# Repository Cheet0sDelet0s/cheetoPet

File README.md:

<h2 align="center"><u>cheetoPet</u></h2>

<h4 align="center"> an esp32 s3 based virtual pet </h4>

<p align="center">

<br>

</p>

### [+] notice
cheetoPet is being completely rebuilt. the pcb and software is still not finished. please star this project and come back to it later!

### [+] description
cheetoPet is a fully open-source modern tamagotchi. it features a 240*280 colour display, 3 face buttons + side rocker, 6 axis gyro and a speaker, all built on a custom pcb.

### [+] software
the software uses an abstraction layer that allows it to be ran on both esp32 and PC, where drivers for different devices can be easily created and swapped in. for PC, a lot of hardware that is present on the cheetoPet board is simulated, such as the gyro and battery. this is so the program runs as close to how it would natively. this is mostly to make development far easier, as constantly having to build the program and wait for it to upload to your esp32 takes a significant amount of time. being able to build and run it locally, while having access to regular c++ debugging tools, makes everything much less annoying.

### [+] building for pc
use the build.sh bash script in cheetoPet-V2:
`./build.sh`
you will need gcc and SDL2 installed. if the build is successful, the executable will run automatically. i develop on linux, so you may have issues if you are on windows/macos. if you are - why? without sounding like an annoying arch user (which i am), linux is simply better.

### [+] uploading to esp32
arduino IDE/CLI or the arduino vscode extension (what i use) is required to build and upload to the board. install the esp32 core in board manager, select esp32s3 dev module as your device, enable USB CDC on boot in tools and upload.

### [+] ordering pcb
i use JLCPCB for all my pcbs. they are simply the cheapest option available, but you can use any service really. just upload the gerbers and probably order a stencil to go with it. no specific board settings are needed really, though you may want to get a lower board thickness.

### [+] ordering parts
LCSC (sister company of jlcpcb)  is where i get my parts for this boardd. aliexpress unfortunately doesnt really work here. its a sad day for us all. there is a BOM you can upload however there are most likely a few parts on it that are out of stock. finding alternatives is fairly easy.

you must buy the battery and display separately. a 1S 1000mah lipo/ion is what the board expects. the display is a very specific ST7789 from BuyDisplay, you can find it on aliexpress thank GOD. https://www.aliexpress.com/item/1005008850313883.html
they are about $5-6 each.

### [+] ordering pcba
i probably wouldnt even bother assembling by hand like i did, however getting it assembled for you is just so expensive for low quantity orders. jlcpcb quoted me £150 ($200, not including battery and display cost) for 2 boards, when building 4 by hand costs £100. so unless you are ordering 1000 units, you are kind of screwed either way 🥰🥰🥰

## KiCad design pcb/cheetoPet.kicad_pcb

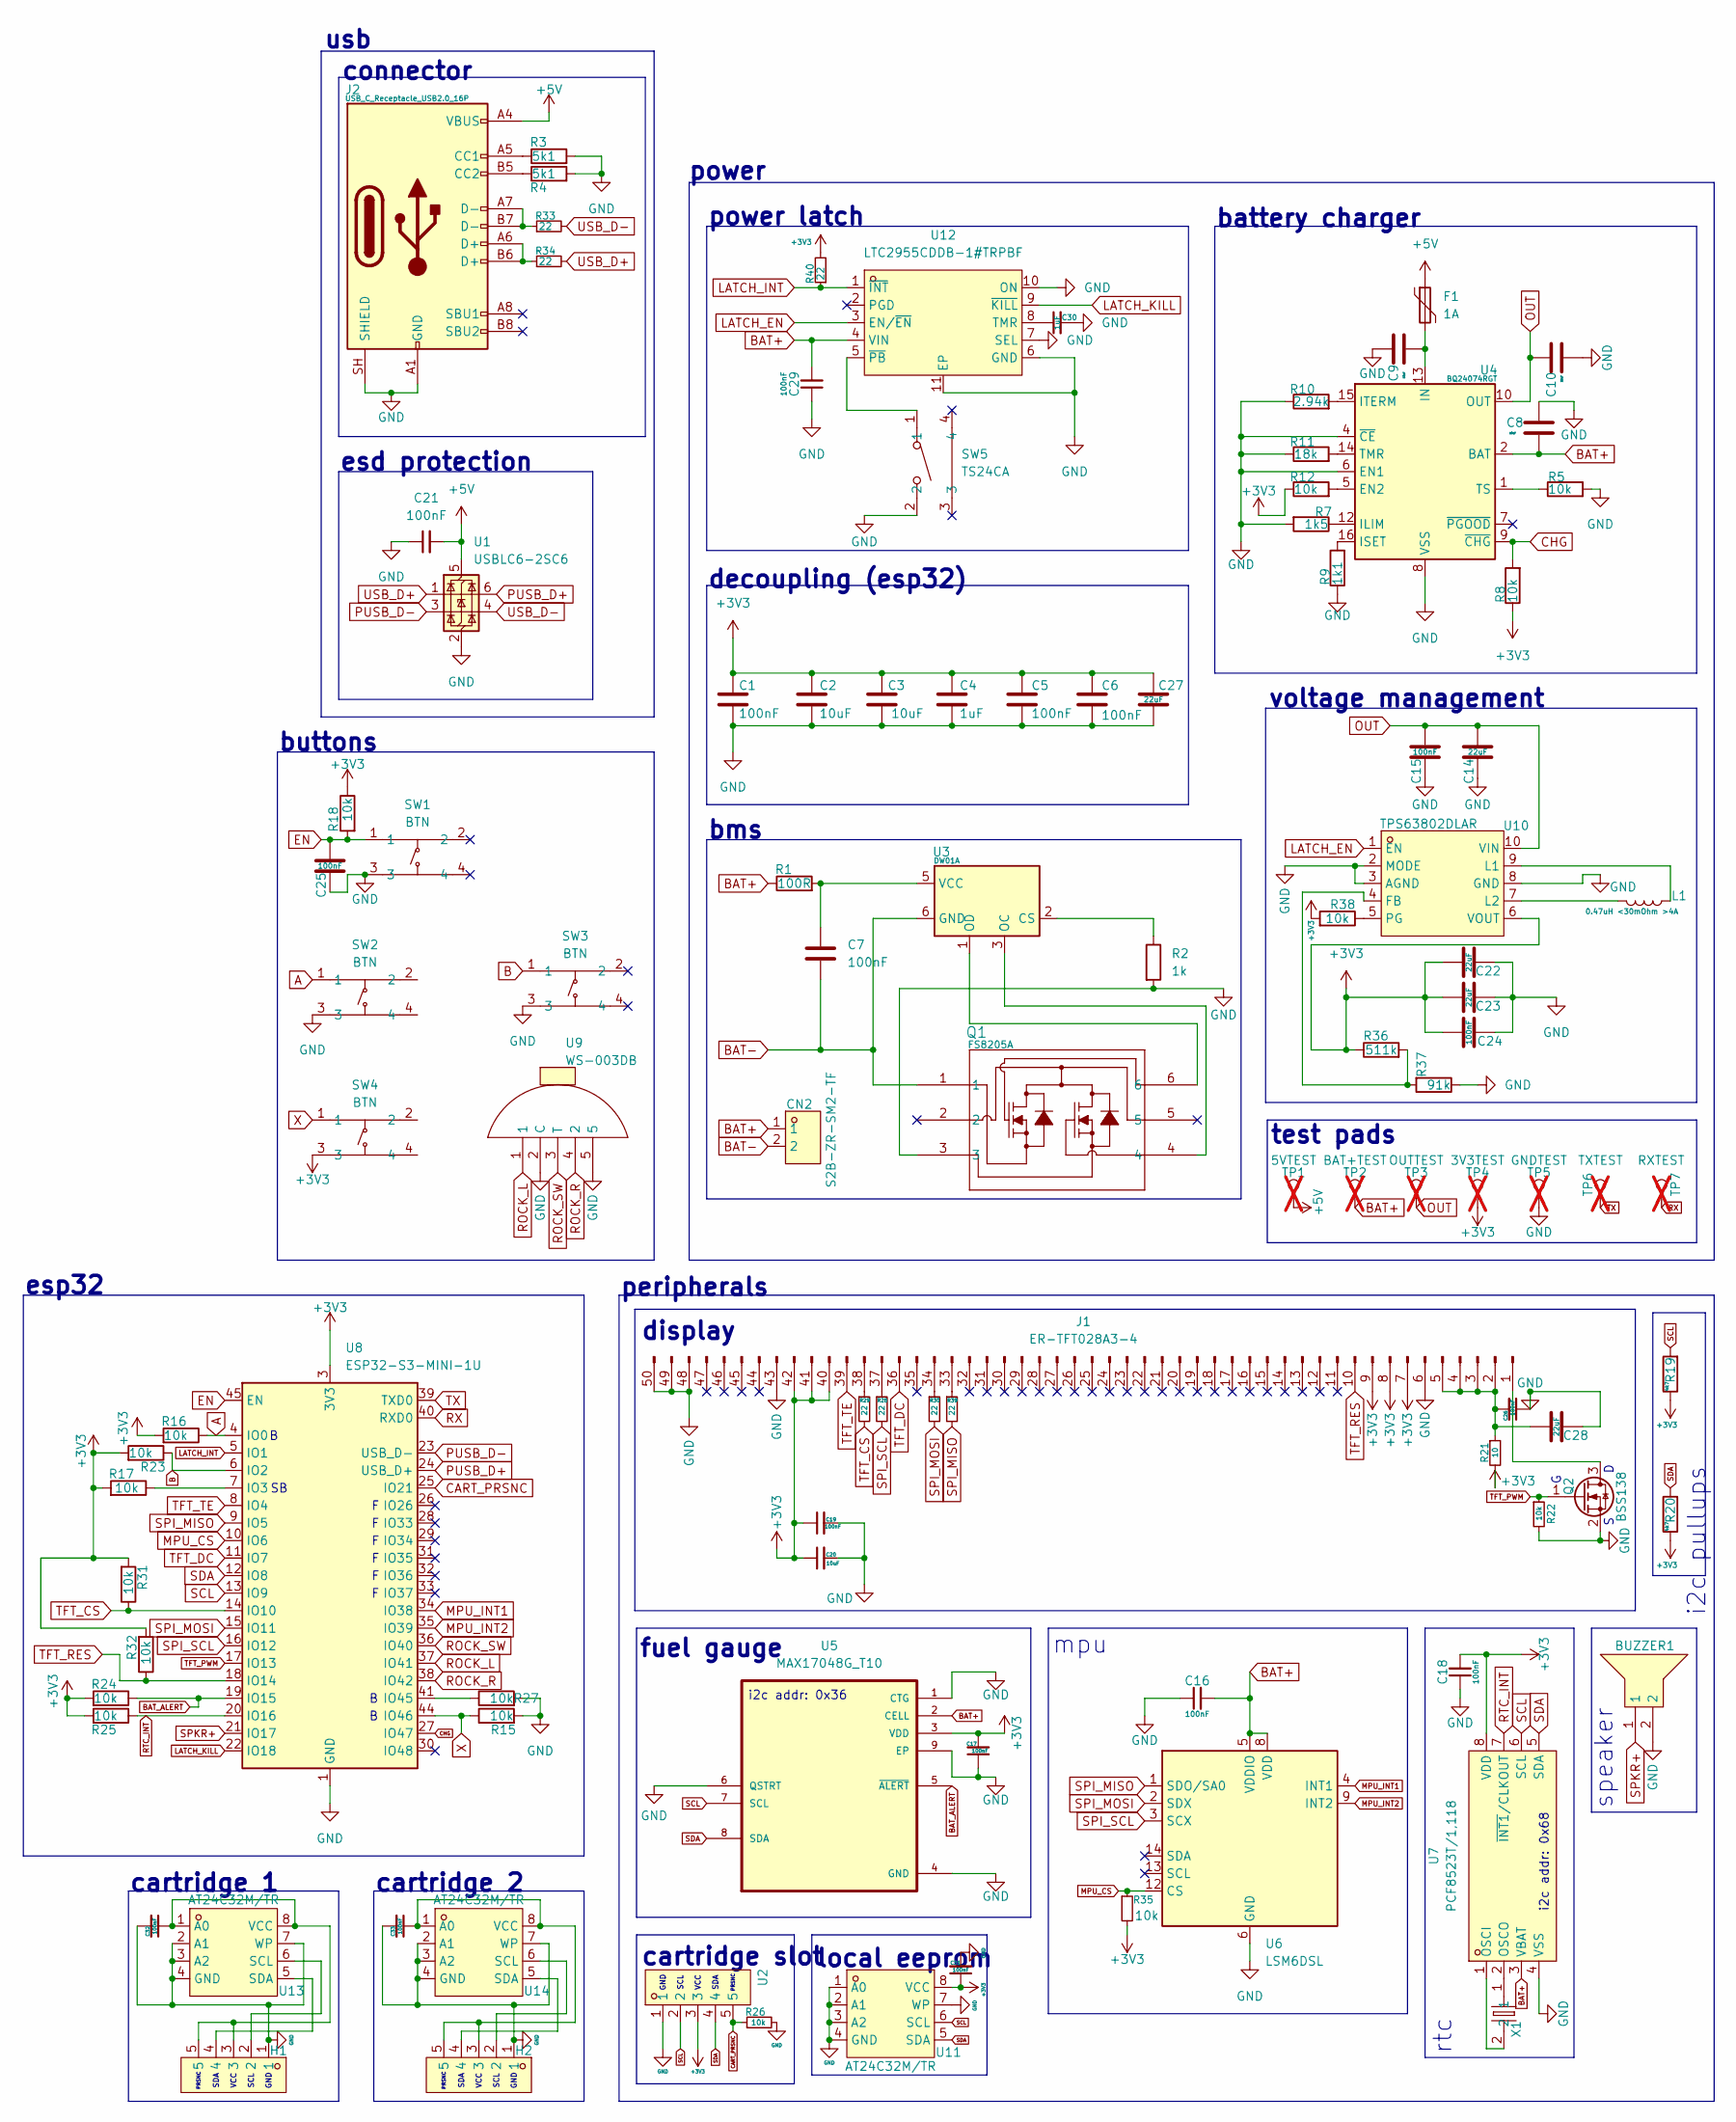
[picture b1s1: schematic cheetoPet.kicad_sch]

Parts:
BUZZER1: CPT-9019A-SMT-TR; BUZ-SMD_L9.0-W9.0_CPT-9019A-SMT-TR; MPN CPT-9019A-SMT-TR; LCSC Part C20181991
C1, C5, C6, C7, C15, C16, C17, C18, C19, C21, C24, C25, C26, C29, C31, C32, C33: 100nF; C_0805_2012Metric - CUSTOM TEXT; LCSC Part C5137467
C2, C3, C8, C9, C20: 10uF; C_0805_2012Metric - CUSTOM TEXT; LCSC Part C15850
C4, C30: 1uF; C_0805_2012Metric - CUSTOM TEXT; LCSC Part C28323
C10, C14, C22, C23, C27, C28: 22uF; C_0805_2012Metric - CUSTOM TEXT; LCSC Part C98190
CN2: S2B-ZR-SM2-TF; CONN-SMD_2P-P1.50_S2B-ZR-SM2-TF-LF-SN; MPN S2B-ZR-SM2-TF(LF)(SN); LCSC Part C594994
F1: 1A; Fuse_1812_4532Metric; LCSC Part C2649901
H1, H2: HX PZ2.54-1X5P WT; HDR-SMD_5P-P2.54-H-M-W12.8-N; MPN HX PZ2.54-1x5P WT; LCSC Part C46061678
J1: ER-TFT028A3-4; FPC-50pin,0.5Pitch
J2: USB_C_Receptacle_USB2.0_16P; USB_C_Receptacle_G-Switch_GT-USB-7010ASV; LCSC Part C2988369
L1: 0.47uH <30mOhm >4A; L1008; LCSC Part C42455362
Q1: FS8205A; SOT-23-6L_TCP; LCSC Part C908265
Q2: BSS138; SOT-23; LCSC Part C7420339
R1: 100R; R_0805_2012Metric - CUSTOM TEXT; LCSC Part C105577
R2: 1k; R_0805_2012Metric - CUSTOM TEXT; LCSC Part C2907232
R3, R4: 5k1; R_0805_2012Metric - CUSTOM TEXT; LCSC Part C27834
R5, R8, R12, R15, R16, R17, R18, R22, R23, R24, R25, R26, R27, R31, R32, R35, R38: 10k; R_0805_2012Metric - CUSTOM TEXT; LCSC Part C2907219
R7: 1k5; R_0805_2012Metric - CUSTOM TEXT; LCSC Part C2907216
R9: 1k1; R_0805_2012Metric - CUSTOM TEXT; LCSC Part C2933286
R10: 2.94k; R_0805_2012Metric - CUSTOM TEXT; LCSC Part C865383
R11: 18k; R_0805_2012Metric - CUSTOM TEXT; LCSC Part C17506
R19, R20: 4k7; R_0805_2012Metric - CUSTOM TEXT; LCSC Part C2907264
R21: 10; R_0805_2012Metric - CUSTOM TEXT; LCSC Part C2907220
R28, R29, R30, R33, R34, R39, R40: 22; R_0805_2012Metric - CUSTOM TEXT; LCSC Part C2907310
R36: 511k; R_0805_2012Metric - CUSTOM TEXT; LCSC Part C5159719
R37: 91k; R_0805_2012Metric - CUSTOM TEXT; LCSC Part C2933509
SW1, SW2, SW3, SW4: BTN; KEY-SMD_4P-L4.2-W2.8-P1.60-LS4.6; MPN KMR621NGLFS; LCSC Part C221692
SW5: TS24CA; SW-SMD_2P-TS24CA; MPN TS24CA; LCSC Part C393942
TP1: 5VTEST; TestPoint_Pad_1.5x1.5mm; not fitted
TP2: BAT+TEST; TestPoint_Pad_1.5x1.5mm; not fitted
TP3: OUTTEST; TestPoint_Pad_1.5x1.5mm; not fitted
TP4: 3V3TEST; TestPoint_Pad_1.5x1.5mm; not fitted
TP5: GNDTEST; TestPoint_Pad_1.5x1.5mm; not fitted
TP6: TXTEST; TestPoint_Pad_1.5x1.5mm; not fitted
TP7: RXTEST; TestPoint_Pad_1.5x1.5mm; not fitted
U1: USBLC6-2SC6; SOT-23-6; LCSC Part C5180249
U2: HX PM2.54-1X5P WT; HDR-SMD_5P-P2.54-H-F; MPN HX PM2.54-1x5P WT; LCSC Part C46061769
U3: DW01A; SOT-23-6; LCSC Part C42380662
U4: BQ24074RGT; VQFN-16-1EP_3x3mm_P0.5mm_EP1.6x1.6mm; LCSC Part C54313
U5: MAX17048G_T10; TDFN-8-1EP_2x2mm_P0.5mm_EP0.8x1.2mm; LCSC Part C2682616
U6: LSM6DSL; LGA-14_3x2.5mm_P0.5mm_LayoutBorder3x4y; LCSC Part C126672
U7: PCF8523T/1,118; SOP-8_L4.9-W3.9-P1.27-LS6.0-BL; MPN PCF8523T/1,118; LCSC Part C2651516
U8: ESP32-S3-MINI-1U; ESP32-S2-MINI-1U; LCSC Part C2980299
U9: WS-003DB; SW-SMD_WS-003DB; MPN WS-003DB; LCSC Part C46598198
U10: TPS63802DLAR; VSON-10_L3.0-W2.0-P0.50-TL; MPN TPS63802DLAR; LCSC Part C2845237
U11, U13, U14: AT24C32M/TR; SOP-8_L4.9-W3.9-P1.27-LS6.0-BL; MPN AT24C32M/TR; LCSC Part C2688466
U12: LTC2955CDDB-1#TRPBF; DFN-10_L3.0-W2.0-P0.50-BL-EP; MPN LTC2955CDDB-1#TRPBF; LCSC Part C683788
X1: SC-32S32.768kHz20PPM7pF; OSC-SMD_L3.2-W1.5; MPN SC-32S32.768kHz20PPM7pF; LCSC Part C97604

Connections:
+3V3: C1.1, C2.1, C3.1, C4.1, C5.1, C6.1, C17.2, C18.2, C19.1, C20.1, C22.1, C23.1, C24.1, C27.2, C31.1, J1.7, J1.8, J1.9, J1.40, J1.41, J1.42, R8.1, R12.1, R16.2, R17.2, R18.1, R19.1, R20.1, R21.2, R23.2, R24.2, R25.2, R31.2, R32.2, R35.2, R36.1, R38.2, R40.2, SW4.3, TP4.1 (1_1), U2.3, U5.3 (VDD), U7.8 (VDD), U8.3 (3V3), U10.6 (VOUT), U11.8 (VCC)
+5V: C21.2, F1.1, J2.A4 (VBUS), J2.A9 (VBUS), J2.B4 (VBUS), J2.B9 (VBUS), TP1.1 (1_1), U1.5 (VBUS)
A: R16.1, SW2.1, U8.4 (IO0)
B: R23.1, SW3.1, U8.6 (IO2)
BAT+: C8.2, C16.2, C29.2, CN2.1, R1.1, TP2.1 (1_1), U4.2 (BAT), U4.3 (BAT), U5.2 (CELL), U6.5 (VDDIO), U6.8 (VDD), U7.3 (VBAT), U12.4 (VIN)
BAT-: C7.2, CN2.2, Q1.1, U3.6 (GND)
BAT_ALERT: R24.1, U5.5 (~ALERT), U8.19 (IO15)
CART_PRSNC: R26.1, U2.5, U8.25 (IO21)
CHG: R8.2, U4.9 (~CHG), U8.27 (IO47)
EN: C25.1, R18.2, SW1.1, U8.45 (EN)
GND: BUZZER1.2, C1.2, C2.2, C3.2, C4.2, C5.2, C6.2, C8.1, C9.1, C10.2, C14.2, C15.2, C16.1, C17.1, C18.1, C19.2, C20.2, C21.1, C22.2, C23.2, C24.2, C25.2, C26.1, C27.1, C28.2, C29.1, C30.2, C31.2, C32.2, C33.2, H1.1, H2.1, J1.6, J1.43, J1.48, J1.49, J1.50, J2.A1 (GND), J2.A12 (GND), J2.B1 (GND), J2.B12 (GND), J2.SH (SHIELD), Q1.3, Q2.2 (S), R2.2, R3.2, R4.2, R5.2, R7.2, R9.1, R10.1, R11.1, R15.2, R22.2, R26.2, R27.2, R37.1, SW1.3, SW2.3, SW3.3, SW5.2, TP5.1 (1_1), U1.2 (GND), U2.1, U4.4 (~CE), U4.6 (EN1), U4.8 (VSS), U4.17 (VSS), U5.1 (CTG), U5.4 (GND), U5.6 (QSTRT), U5.9 (EP), U6.6 (GND), U6.7 (GND), U7.4 (VSS), U8.1 (GND), U8.2 (GND), U8.42 (GND), U8.43 (GND), U8.46 (GND), U8.47 (GND), U8.48 (GND), U8.49 (GND), U8.50 (GND), U8.51 (GND), U8.52 (GND), U8.53 (GND), U8.54 (GND), U8.55 (GND), U8.56 (GND), U8.57 (GND), U8.58 (GND), U8.59 (GND), U8.60 (GND), U8.61 (GND), U8.62 (GND), U8.63 (GND), U8.64 (GND), U8.65 (GND), U9.2 (C), U9.5, U10.2 (MODE), U10.3 (AGND), U10.8 (GND), U11.1 (A0), U11.2 (A1), U11.3 (A2), U11.4 (GND), U11.7 (WP), U12.6 (GND), U12.7 (SEL), U12.10 (ON), U12.11 (EP), U13.2 (A1), U13.3 (A2), U13.4 (GND), U13.7 (WP), U14.2 (A1), U14.3 (A2), U14.4 (GND), U14.7 (WP)
LATCH_EN: U10.1 (EN), U12.3 (EN/~EN)
LATCH_INT: R40.1, U8.5 (IO1), U12.1 (~INT)
LATCH_KILL: U8.22 (IO18), U12.9 (~KILL)
MPU_CS: R35.1, U6.12 (CS), U8.10 (IO6)
MPU_INT1: U6.4 (INT1), U8.34 (IO38)
MPU_INT2: U6.9 (INT2), U8.35 (IO39)
unnamed: J1.1, Q2.3 (D)
unnamed: C26.2, C28.1, J1.2, J1.3, J1.4, J1.5, R21.1
unnamed: J1.33, R39.1
unnamed: J1.34, R30.1
unnamed: J1.37, R28.1
unnamed: J1.38, R29.1
unnamed: J2.A5 (CC1), R3.1
unnamed: J2.B5 (CC2), R4.1
unnamed: J2.A6 (D+), J2.B6 (D+), R34.1
unnamed: J2.A7 (D-), J2.B7 (D-), R33.1
unnamed: R2.1, U3.2 (CS)
unnamed: Q1.4, U3.3 (OC)
unnamed: Q1.6, U3.1 (OD)
unnamed: C7.1, R1.2, U3.5 (VCC)
unnamed: R12.2, U4.5 (EN2)
unnamed: R7.1, U4.12 (ILIM)
unnamed: C9.2, F1.2, U4.13 (IN)
unnamed: R9.2, U4.16 (ISET)
unnamed: R10.2, U4.15 (ITERM)
unnamed: R11.2, U4.14 (TMR)
unnamed: R5.1, U4.1 (TS)
unnamed: U7.1 (OSCI), X1.2
unnamed: U7.2 (OSCO), X1.1
unnamed: R17.1, U8.7 (IO3)
unnamed: R27.1, U8.41 (IO45)
unnamed: R36.2, R37.2, U10.4 (FB)
unnamed: L1.2, U10.9 (L1)
unnamed: L1.1, U10.7 (L2)
unnamed: R38.1, U10.5 (PG)
unnamed: C30.1, U12.8 (TMR)
unnamed: SW5.1, U12.5 (~PB)
unnamed: C32.1, H1.3, H1.5, U13.1 (A0), U13.8 (VCC)
unnamed: H1.2, U13.6 (SCL)
unnamed: H1.4, U13.5 (SDA)
unnamed: C33.1, H2.3, H2.5, U14.1 (A0), U14.8 (VCC)
unnamed: H2.2, U14.6 (SCL)
unnamed: H2.4, U14.5 (SDA)
OUT: C10.1, C14.1, C15.1, TP3.1 (1_1), U4.10 (OUT), U4.11 (OUT), U10.10 (VIN)
PUSB_D+: U1.6 (I/O1), U8.24 (USB_D+)
PUSB_D-: U1.3 (I/O2), U8.23 (USB_D-)
ROCK_L: U8.37 (IO41), U9.1
ROCK_R: U8.38 (IO42), U9.4 (2)
ROCK_SW: U8.36 (IO40), U9.3 (T)
RTC_INT: R25.1, U7.7 (~INT1/CLKOUT), U8.20 (IO16)
RX: TP7.1 (1_1), U8.40 (RXD0)
SCL: R19.2, U2.2, U5.7 (SCL), U7.6 (SCL), U8.13 (IO9), U11.6 (SCL)
SDA: R20.2, U2.4, U5.8 (SDA), U7.5 (SDA), U8.12 (IO8), U11.5 (SDA)
SPI_MISO: R39.2, U6.1 (SDO/SA0), U8.9 (IO5)
SPI_MOSI: R30.2, U6.2 (SDX), U8.15 (IO11)
SPI_SCL: R28.2, U6.3 (SCX), U8.16 (IO12)
SPKR+: BUZZER1.1, U8.21 (IO17)
TFT_CS: R29.2, R31.1, U8.14 (IO10)
TFT_DC: J1.36, U8.11 (IO7)
TFT_PWM: Q2.1 (G), R22.1, U8.17 (IO13)
TFT_RES: J1.10, R32.1, U8.18 (IO14)
TFT_TE: J1.39, U8.8 (IO4)
TX: TP6.1 (1_1), U8.39 (TXD0)
USB_D+: R34.2, U1.1 (I/O1)
USB_D-: R33.2, U1.4 (I/O2)
X: R15.1, SW4.1, U8.44 (IO46)

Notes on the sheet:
cartridge slot
VCC
SCL
fuel gauge
peripherals
voltage management
GND
i2c pullups
display
power
speaker
SDA
usb
bms
mpu
i2c addr: 0x68
cartridge 2
esd protection
esp32
PRSNC
test pads
local eeprom
i2c addr: 0x36
connector
decoupling (esp32)
rtc
power latch
battery charger
buttons
cartridge 1

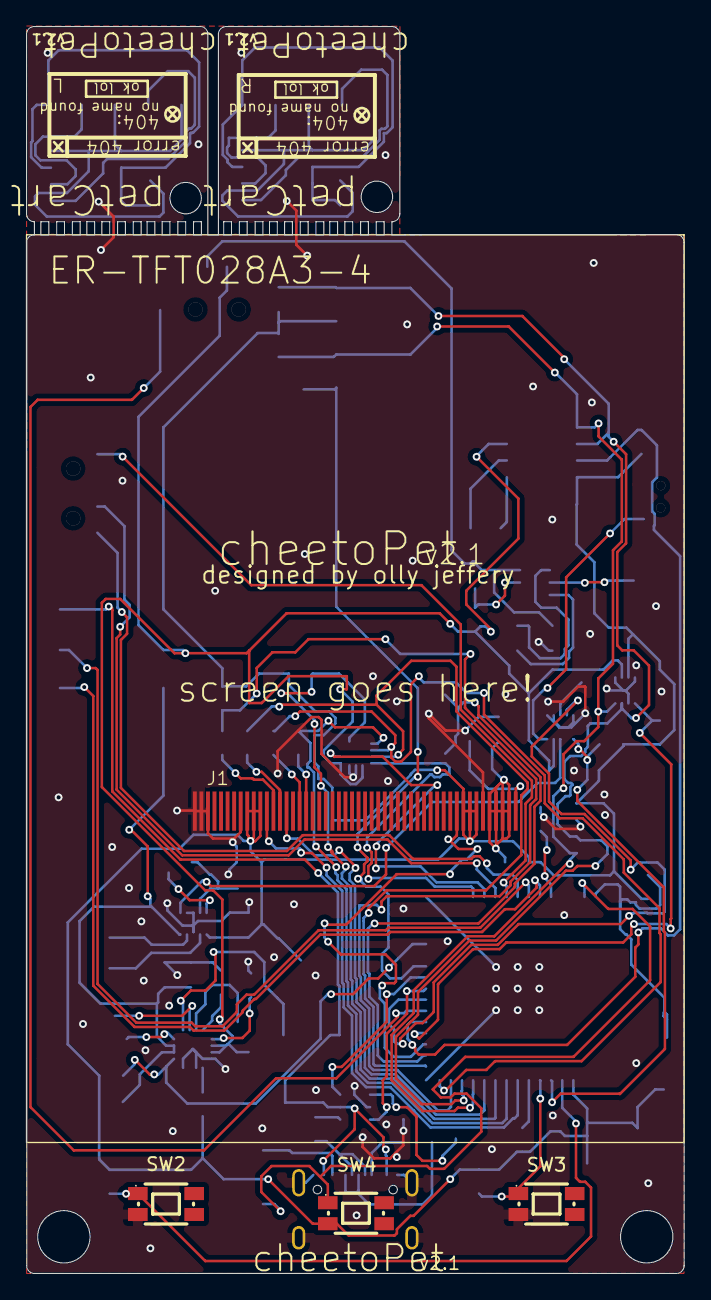
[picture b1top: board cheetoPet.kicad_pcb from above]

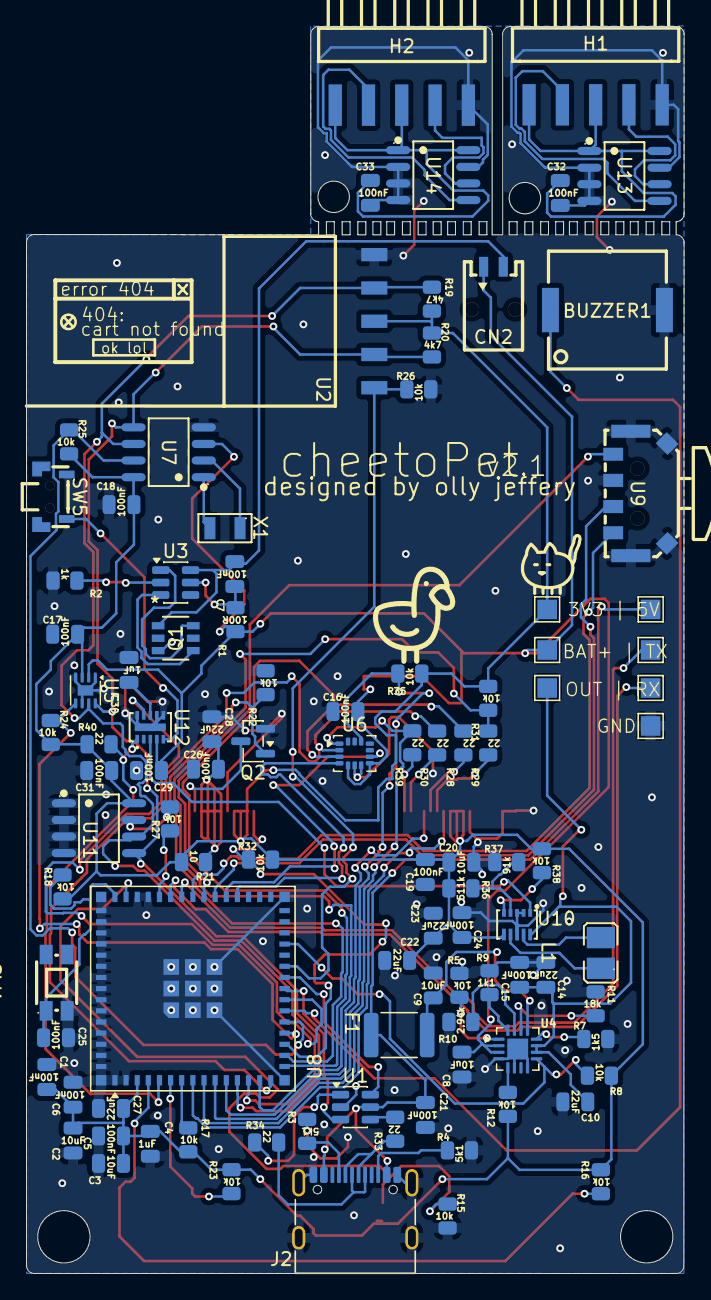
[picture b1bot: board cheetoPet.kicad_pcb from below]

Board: 2 copper layers, 50.2 x 95.2 mm, 104 parts (100 on the bottom side), 77 nets.

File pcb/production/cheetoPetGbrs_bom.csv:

Designator,Footprint,Quantity,Value,LCSC Part #
"C1, C11, C15, C16, C18, C21, C24, C25, C5, C6, C7",0402,11,100nF,C1525
"C10, C14, C22, C23, C27, C28",0805,6,22uF,C59461
"C12, C2, C20, C3",0603,4,10uF,C19702
"C17, C19, C26",0402,3,0.1uF,C1525
C4,0402,1,1uF,C52923
"C8, C9",0603,2,10uF X5R,C19702
CN1,CONN-SMD_P2.00_S2B-PH-SM4-TB-LF-SN,1,bat connector,C295747
F1,1812,1,1A,C2649901
FPC1,FPC-SMD_12P-P0.50_FPC-05F-12PH20,1,FPC-05F-12PH20,C2856799
J2,USB_C_Receptacle_G-Switch_GT-USB-7010ASV,1,USB_C_Receptacle_USB2.0_16P,C2988369
L1,L1008,1,0.47uH <30mOhm >4A,C42455362
Q1,SOT-23-6L_TCP,1,FS8205A,C908265
Q2,SOT-23,1,BSS138,C7420339
R1,0402,1,100R,C25076
R10,0402,1,2.94k,C22369428
R11,0402,1,18k,C25762
"R12, R13, R15, R16, R17, R18, R22, R23, R24, R25, R26, R27, R31, R32, R35, R38, R5, R8",0402,18,10k,C25744
"R19, R20",0402,2,4k7,C25900
R2,0402,1,1k,C11702
R21,0402,1,10,C25077
"R28, R29, R30, R33, R34",0402,5,22,C25092
"R3, R4",0402,2,5k1,C25905
R36,0402,1,511k,C144750
R37,0402,1,91k,C22356211
R6,0402,1,0,C17168
R7,0402,1,1k5,C25867
R9,0402,1,1k1,C174192
SW1,SW-SMD_LXTD-0204-034,1,POWER,C7498205
SW10,SW-SMD_5P-L4.2-W2.8-P1.60-LS4.6-TR,1,RESET,C221678
SW7,SW-SMD_5P-L4.2-W2.8-P1.60-LS4.6-TR,1,B,C221678
SW8,SW-SMD_5P-L4.2-W2.8-P1.60-LS4.6-TR,1,A,C221678
SW9,SW-SMD_5P-L4.2-W2.8-P1.60-LS4.6-TR,1,X,C221678
U1,SOT-23-6,1,USBLC6-2SC6,C5180249
U10,VSON-10_L3.0-W2.0-P0.50-TL,1,TPS63802DLAR,C2845237
U11,BUZ-SMD_4P-L13.0-W13.0-P11.4-BL,1,KLJ-01304T-08R07W,C18186315
U2,TQFN-16-1EP_3x3mm_P0.5mm_EP1.23x1.23mm,1,MAX98357A,C910544
U3,SOT-23-6,1,DW01A,C42380662
U4,VQFN-16-1EP_3x3mm_P0.5mm_EP1.6x1.6mm,1,BQ24074RGT,C2861252
U5,TDFN-8-1EP_2x2mm_P0.5mm_EP0.8x1.2mm,1,MAX17048G_T10,C2682616
U6,LGA-14_3x2.5mm_P0.5mm_LayoutBorder3x4y,1,LSM6DSL,C126672
U7,MicroCrystal_C7_SON-8_1.5x3.2mm_P0.9mm,1,RV-3028-C7,C3019759
U8,ESP32-S2-MINI-1U,1,ESP32-S3-MINI-1U,C2980299
U9,SW-SMD_WS-003DB,1,WS-003DB,C46598198

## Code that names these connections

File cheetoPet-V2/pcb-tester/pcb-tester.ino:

// #include <ESP_I2S.h>
// #include <math.h>

// I2SClass I2S;

// // MAX98357A connections
// constexpr int PIN_BCLK  = 17;
// constexpr int PIN_LRCLK = 18;
// constexpr int PIN_DOUT  = 21;
// constexpr int PIN_SD    = 13;

// constexpr uint32_t SAMPLE_RATE = 44100;
// constexpr float TONE_FREQ = 440.0f;
// constexpr int16_t AMPLITUDE = 12000;


// #define I2C_SDA_PIN 8
// #define I2C_SCL_PIN 9

// #define A_BUTTON_PIN 0
// #define B_BUTTON_PIN 2
// #define X_BUTTON_PIN 46

// #define ROCK_L_PIN 41
// #define ROCK_R_PIN 42
// #define ROCK_SW_PIN 40

// void setup() {
//     Serial.begin(115200);
//     delay(500);
//     Serial.println("Hello world! Initing i2c");
//     delay(500);

//     pinMode(I2C_SDA_PIN, OUTPUT);
//     pinMode(I2C_SCL_PIN, OUTPUT);

//     pinMode(A_BUTTON_PIN, INPUT);
//     pinMode(B_BUTTON_PIN, INPUT);
//     pinMode(X_BUTTON_PIN, INPUT);
    
//     pinMode(ROCK_L_PIN, INPUT_PULLUP);
//     pinMode(ROCK_R_PIN, INPUT_PULLUP);
//     pinMode(ROCK_SW_PIN, INPUT_PULLUP);
    
//     digitalWrite(I2C_SDA_PIN, LOW);
//     digitalWrite(I2C_SCL_PIN, LOW);
//     // Wire.begin(8, 9);

//     pinMode(PIN_SD, OUTPUT);
//     digitalWrite(PIN_SD, HIGH);    // Enable amplifier

//     // BCLK, LRCLK, DOUT, DIN (unused), MCLK (unused)
//     I2S.setPins(PIN_BCLK, PIN_LRCLK, PIN_DOUT, -1, -1);

//     if (!I2S.begin(
//             I2S_MODE_STD,
//             SAMPLE_RATE,
//             I2S_DATA_BIT_WIDTH_16BIT,
//             I2S_SLOT_MODE_STEREO))
//     {
//         while (true) {
//         delay(100);
//         }
//     }
// }

// void showButtonStatus(int pin, String name, bool active) {
//     Serial.print(name);
//     Serial.print(" button state: ");
//     if (digitalRead(pin) == active) {
//         Serial.println("pressed");
//     } else {
//         Serial.println("not pressed");
//     }
// }

// void loop() {
//     // Wire.beginTransmission(0x36);
//     // Serial.println(Wire.endTransmission());

//     // Wire.beginTransmission(0x52);
//     // Serial.println(Wire.endTransmission());
//     Serial.println("running blah blah blah");

//     showButtonStatus(A_BUTTON_PIN, "A", false);
//     showButtonStatus(B_BUTTON_PIN, "B", false);
//     showButtonStatus(X_BUTTON_PIN, "X", true);
//     showButtonStatus(ROCK_L_PIN, "rocker left", false);
//     showButtonStatus(ROCK_R_PIN, "rocker right", false);
//     showButtonStatus(ROCK_SW_PIN, "rocker button", false);

//     Serial.println();
    
//     constexpr int SAMPLES = 256;
//     int16_t buffer[SAMPLES * 2];   // Stereo interleaved

//     static float phase = 0.0f;
//     const float phaseInc = 2.0f * PI * TONE_FREQ / SAMPLE_RATE;

//     for (int i = 0; i < SAMPLES; i++) {
//         int16_t sample = (int16_t)(AMPLITUDE * sinf(phase));

//         buffer[2 * i]     = sample;   // Left
//         buffer[2 * i + 1] = sample;   // Right

//         phase += phaseInc;
//         if (phase >= 2.0f * PI)
//         phase -= 2.0f * PI;
//     }

//     I2S.write((uint8_t *)buffer, sizeof(buffer));
// }

#include <LovyanGFX.hpp>

class LGFX : public lgfx::LGFX_Device
{
  lgfx::Panel_ST7789 _panel_instance;
  lgfx::Bus_SPI _bus_instance;

public:

  LGFX(void)
  {
    {
      auto cfg = _bus_instance.config();

      cfg.spi_host = SPI2_HOST;   // ESP32-S3 FSPI
      cfg.spi_mode = 3;
      cfg.freq_write = 27000000;
      cfg.freq_read = 16000000;

      cfg.pin_sclk = 12;
      cfg.pin_mosi = 11;
      cfg.pin_miso = -1;
      cfg.pin_dc   = 7;

      _bus_instance.config(cfg);
      _panel_instance.setBus(&_bus_instance);
    }

    {
      auto cfg = _panel_instance.config();

      cfg.pin_cs   = 10;
      cfg.pin_rst  = 14;

      cfg.panel_width  = 240;
      cfg.panel_height = 280;

      cfg.offset_x = 0;
      cfg.offset_y = 0;

      cfg.invert = true;      // common for ST7789
      cfg.rgb_order = false; // try true if colours are swapped

      _panel_instance.config(cfg);
    }

    setPanel(&_panel_instance);
  }
};

LGFX tft;


void setup()
{
  Serial.begin(115200);
  delay(1000);

  Serial.println("LovyanGFX start");

  tft.init();

  Serial.println("Display init OK");

  tft.setRotation(0);

  tft.fillScreen(TFT_WHITE);

  tft.setTextColor(TFT_BLACK);
  tft.setTextSize(2);

  tft.drawString("ESP32-S3", 20, 20);
  tft.drawString("ST7789 240x280", 20, 50);

  tft.fillCircle(120, 140, 50, TFT_RED);
  tft.fillRect(70, 210, 100, 30, TFT_BLUE);
}

void loop()
{
}

// #include <SPI.h>

// // Pin definitions
// #define PIN_MISO 5
// #define PIN_MOSI 11
// #define PIN_SCK  12
// #define PIN_CS   6
// #define PIN_INT1 38
// #define PIN_INT2 39

// SPIClass spi(FSPI);

// // LSM6DSL registers
// #define WHO_AM_I      0x0F
// #define CTRL1_XL      0x10
// #define CTRL2_G       0x11
// #define CTRL3_C       0x12

// #define OUTX_L_G      0x22
// #define OUTX_L_XL     0x28

// // Expected device ID
// #define LSM6DSL_ID    0x6A

// void writeReg(uint8_t reg, uint8_t value) {
//   digitalWrite(PIN_CS, LOW);
//   spi.beginTransaction(SPISettings(100000, MSBFIRST, SPI_MODE3));
//   spi.transfer(reg & 0x7F); // Write
//   spi.transfer(value);
//   spi.endTransaction();
//   digitalWrite(PIN_CS, HIGH);
// }

// uint8_t readReg(uint8_t reg) {
//   digitalWrite(PIN_CS, LOW);
//   spi.beginTransaction(SPISettings(100000, MSBFIRST, SPI_MODE3));
//   spi.transfer(reg | 0x80); // Read
//   uint8_t value = spi.transfer(0);
//   spi.endTransaction();
//   digitalWrite(PIN_CS, HIGH);
//   return value;
// }

// void readRegs(uint8_t reg, uint8_t *buffer, uint8_t length) {
//   digitalWrite(PIN_CS, LOW);
//   spi.beginTransaction(SPISettings(100000, MSBFIRST, SPI_MODE3));
//   spi.transfer(reg | 0xC0); // Read + auto-increment
//   for (int i = 0; i < length; i++) {
//     buffer[i] = spi.transfer(0);
//   }
//   spi.endTransaction();
//   digitalWrite(PIN_CS, HIGH);
// }

// void setup() {
//   Serial.begin(115200);
//   delay(1000);

//   pinMode(PIN_CS, OUTPUT);
//   digitalWrite(PIN_CS, HIGH);

//   pinMode(PIN_INT1, INPUT);
//   pinMode(PIN_INT2, INPUT);

//   spi.begin(PIN_SCK, PIN_MISO, PIN_MOSI, PIN_CS);

//   Serial.println("LSM6DSL SPI Test");

//   uint8_t id = readReg(WHO_AM_I);

//   Serial.print("WHO_AM_I = 0x");
//   Serial.println(id, HEX);

//   if (id != LSM6DSL_ID) {
//     Serial.println("ERROR: Device not found!");

//     for (int reg = 0x0F; reg <= 0x12; reg++) {
//       Serial.print("0x");
//       Serial.print(reg, HEX);
//       Serial.print(" = 0x");
//       Serial.println(readReg(reg), HEX);
//     }
//     while (1) delay(100);
//   }

//   Serial.println("Device detected.");

//   // Enable register auto increment (IF_INC = bit2)
//   writeReg(CTRL3_C, 0x04);

//   // Accelerometer:
//   // ODR = 104 Hz
//   // ±2 g
//   writeReg(CTRL1_XL, 0x40);

//   // Gyroscope:
//   // ODR = 104 Hz
//   // ±250 dps
//   writeReg(CTRL2_G, 0x40);

//   delay(100);

//   Serial.println("Sensors enabled.");
// }

// void loop() {
//   uint8_t data[12];

//   // Read gyro + accel
//   readRegs(OUTX_L_G, data, 12);

//   int16_t gx = (int16_t)(data[1] << 8 | data[0]);
//   int16_t gy = (int16_t)(data[3] << 8 | data[2]);
//   int16_t gz = (int16_t)(data[5] << 8 | data[4]);

//   int16_t ax = (int16_t)(data[7] << 8 | data[6]);
//   int16_t ay = (int16_t)(data[9] << 8 | data[8]);
//   int16_t az = (int16_t)(data[11] << 8 | data[10]);

//   Serial.print("Accel: ");
//   Serial.print(ax);
//   Serial.print(", ");
//   Serial.print(ay);
//   Serial.print(", ");
//   Serial.print(az);

//   Serial.print("   Gyro: ");
//   Serial.print(gx);
//   Serial.print(", ");
//   Serial.print(gy);
//   Serial.print(", ");
//   Serial.println(gz);

//   delay(100);
// }

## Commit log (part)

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2025-06-07 added ino
2025-06-07 md test
2025-06-07 behaviour tree update, pet movement, and speech bubble update
2025-06-07 ui stuff, behaviour tree, fixes, speech lines
2025-06-08 inventory display fixes
2025-06-08 moved bitmaps and voice lines to seperate files, fixed food inventory
2025-06-08 food placing broke whoops
2025-06-08 beginnings of shop, voice line fix
2025-06-09 shop expansion, goose wanders about now
2025-06-10 shop works now, goose can turn around, walking animations, new voice lines
2025-06-10 added pong game, complaining about being bored in behaviour tree
2025-06-12 added death, fixes, boot sequence changed
2025-06-13 settings page, edit date and time
2025-06-13 beginning of pong pet leveling
2025-06-14 bug fixes, pong addons, complaining about sleep, accelerometer, g force death, eeprom testing
2025-06-15 saving game to RTC EEPROM works now, bug fixes
2025-06-15 saving done in minute intervals, can be changed in save manager in settings, although the page is slightly broken
2025-06-16 slight pong rebalance, drawCenteredButton() fixed, saving fixes
2025-06-16 pong moved to seperate h and cpp files, another rebalance (when will it end)
2025-06-16 begun making veridium, game library inventory, and random sentence generation
2025-06-16 yooo veridium shooting works and is awesome!
2025-06-17 veridium updates, pet line updates
2025-06-17 hotfix
2025-06-18 sitting on couch
2025-06-19 pet mask fixes
2025-06-21 added sprites
2025-06-21 readme update, removed old battery handling stuff
2025-06-23 pet hunger goes down slower
2025-06-23 pet no longer goes braindead after trying to sit on chair, pong fixes
2025-06-24 dads pushed my changes
2025-06-24 sitting by fireplace, refactors
2025-06-26 flappy bird, fixes
2025-06-27 flappy bird fixes, new images to be used later
2025-06-27 sandbox
2025-06-28 case stls added, photos added
2025-06-28 compressed images
2025-06-28 before refactor
2025-06-28 placed items refactor, particle sim overhaul
2025-07-01 refactor in progress, item placement completely borked
2025-07-02 drawing works, outside works, awesome stuff, latin project temporary
2025-08-15 added speaker, some changes and stuff, working on pcb
2025-08-17 audio engine changes, bubblebox changes, added piano + ode to joy, bug fixes, other stuff probs
2025-08-17 audio engine now uses Note struct
2025-08-17 added UNFINISHED pcb files
2025-08-18 added screen recording through serial and python, added screenshot
2025-08-18 add photo
2025-08-24 refactoring in progress
2025-08-24 settings refactor complete, moving on to menu system
2025-08-24 huge menu overhaul, added more comments
2025-08-24 added blog post link to readme
2025-08-24 started refactoring item system - go back one commit for working version
2025-08-25 item placing system overhaul/refactor, now uses vector arrays, way more modular. new save method supporting vector arrays
2025-08-26 Revert "item placing system overhaul/refactor, now uses vector arrays, way more modular. new save method supporting vector arrays"
    This reverts commit 8ab486616fa2d7bac33ae61a4c4b6721c42b7214.
2025-08-26 Reapply "item placing system overhaul/refactor, now uses vector arrays, way more modular. new save method supporting vector arrays"
    This reverts commit 063ed46f4e698d4804b3e3085a5a949ec7c7e57e.
2025-08-26 added cursor snapping to buttons/interaction points, bug fixes
2025-08-27 added pooping, fixed system crashing after pooping, snapping
2025-08-28 added ibom
2025-08-30 bleh
2025-09-11 pcb updates, other stuff idfk
2025-09-13 so much stuff! added particle system, new mouse toggle mode, procedual news, bug fixes, deleting items
2025-09-13 multiple pets to choose from! procedural news! all kinds of stuff!
2025-09-14 pet stuff
2025-09-16 3D engine updates
2025-09-28 idk whats changed but some stuff has
2026-01-11 boot menu, moved code into new folder
2026-01-12 begun development of V2 ino
2026-01-13 started adding hardware functions to V2
2026-01-13 remove ibom
2026-01-13 remove ibom attempt 2
2026-01-15 menu system is working, huge import of pet stuff as well
2026-01-15 BASE PET SYSTEM WORKS. updating pet and drawing are seperate (thank god), starting to work on making new menus and stuff
2026-01-16 adding menus and stuff
2026-01-17 ITEM PLACING FINISHED! and settings menu and stufffff
2026-01-17 item placing fully fully done now with support for food. shop split into different sections
2026-01-19 NEW PCB v0.3, pretty much finished, also some code changes (i think safe crack game which is rubbish)
2026-06-28 new pcb lol
2026-06-29 removed weird ass plugin files
